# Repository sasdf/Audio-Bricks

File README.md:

Audio-Bricks
============

Building your own custom audio devices just like playing bricks

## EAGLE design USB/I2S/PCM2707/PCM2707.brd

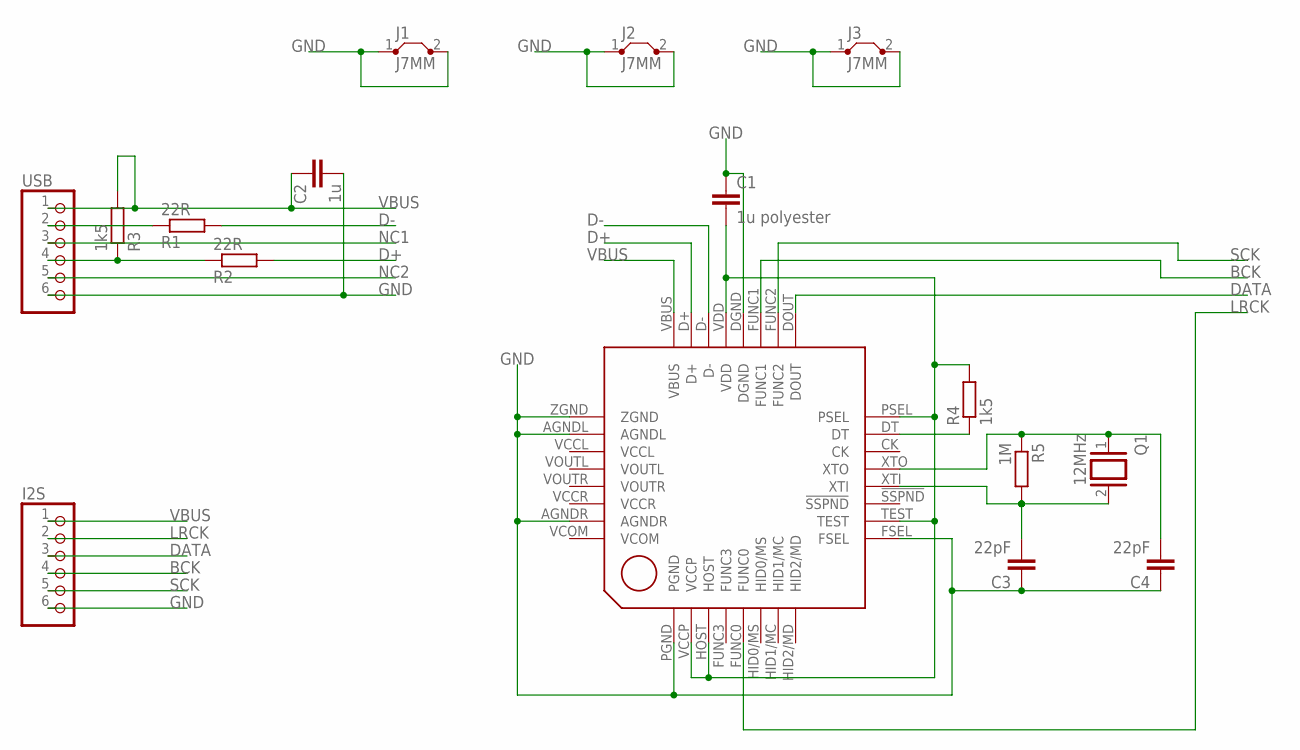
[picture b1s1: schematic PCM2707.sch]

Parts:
C1: 1u polyester; C5B4.5
C2: 1u; C5B3.5
C3, C4: 22pF; C5B3.5
I2S: PINHD-1X6/90; 1X06/90
J1, J2, J3: J7MM; 07
Q1: 12MHz; Q
R1, R2: 22R; 0207/7
R3, R4: 1k5; 0207/7
R5: 1M; 0207/7
U$1: PCM2706; TQFP32-08
USB: PINHD-1X6; 1X06

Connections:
BCK: I2S.4, U$1.FUNC1
D+: R2.2, U$1.D+
D-: R1.2, U$1.D-
DATA: I2S.3, U$1.DOUT
GND: C1.1, C2.2, C3.1, C4.1, I2S.6, J1.1, J1.2, J2.1, J2.2, J3.1, J3.2, U$1.AGNDL, U$1.AGNDR, U$1.DGND, U$1.FSEL, U$1.PGND, U$1.ZGND, USB.6
LRCK: I2S.2, U$1.FUNC0
unnamed: C1.2, R4.2, U$1.HOST, U$1.PSEL, U$1.TEST, U$1.VCCP, U$1.VDD
unnamed: R4.1, U$1.DT
unnamed: C4.2, Q1.1, R5.1, U$1.XTO
unnamed: R2.1, R3.1, USB.4
unnamed: C3.2, Q1.2, R5.2, U$1.XTI
unnamed: R1.1, USB.2
NC1: USB.3
NC2: USB.5
SCK: I2S.5, U$1.FUNC2
VBUS: C2.1, I2S.1, R3.2, U$1.VBUS, USB.1
VCCL: U$1.VCCL
VCCR: U$1.VCCR
VCOM: U$1.VCOM

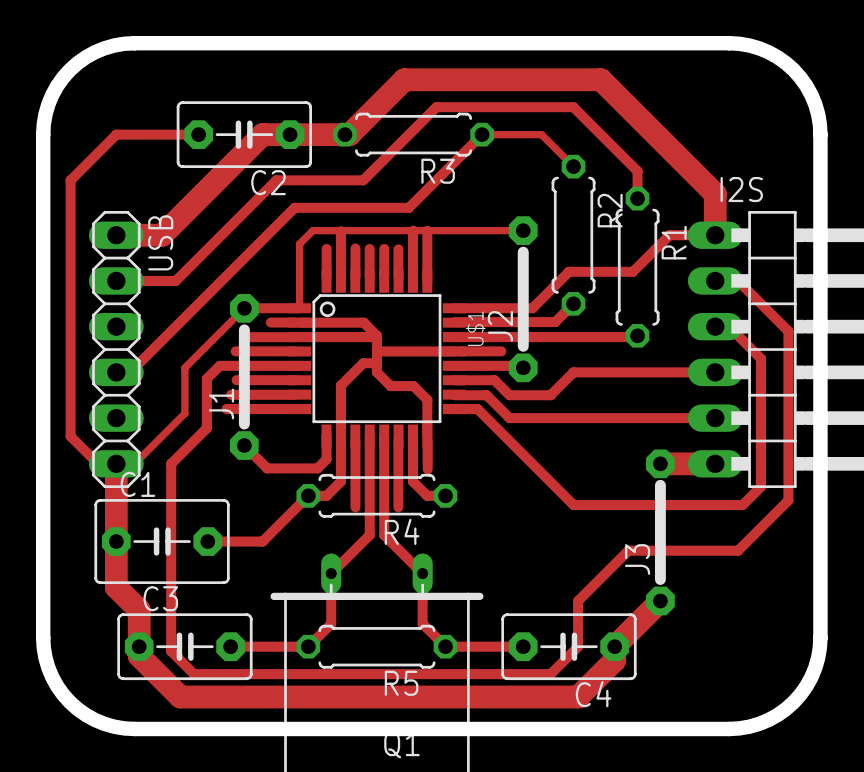
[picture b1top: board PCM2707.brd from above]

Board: 2 copper layers, 43.2 x 38.1 mm, 16 parts (0 on the bottom side), 14 nets.

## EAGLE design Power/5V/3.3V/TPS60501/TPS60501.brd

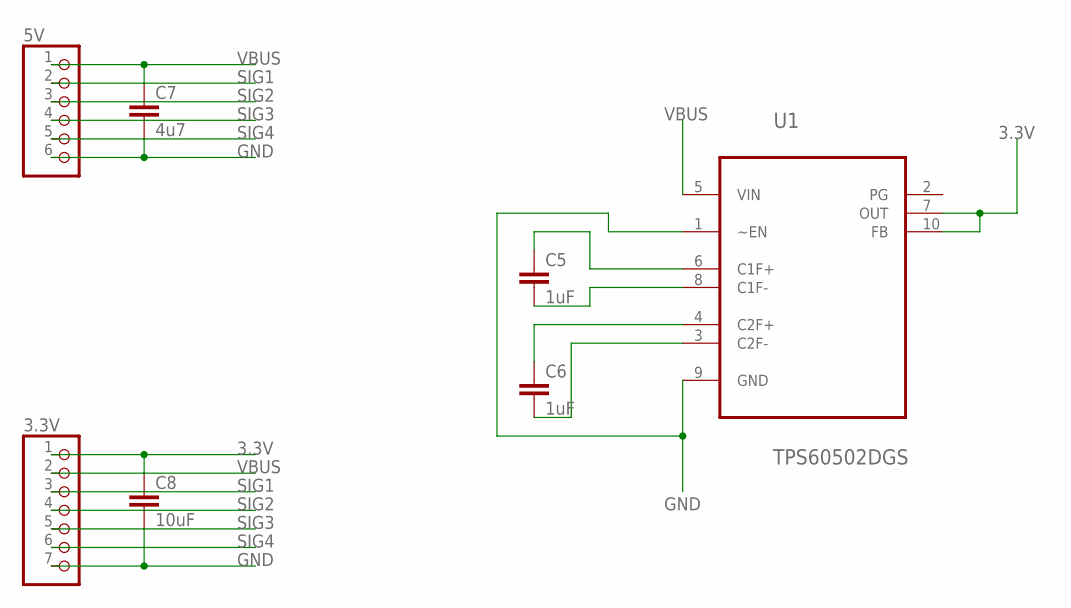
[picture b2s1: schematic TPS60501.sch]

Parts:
3.3V: PINHD-1X7; 1X07
5V: PINHD-1X6; 1X06
C5, C6: 1uF; C025-050X050
C7: 4u7; C025-050X050
C8: 10uF; C025-050X050
U1: TPS60502DGS; SOP50P490X110-10N

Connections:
3.3V: 3.3V.1, C8.1, U1.7 (OUT), U1.10 (FB)
GND: 3.3V.7, 5V.6, C7.2, C8.2, U1.1 (~EN), U1.9 (GND)
unnamed: C5.1, U1.6 (C1F+)
unnamed: C5.2, U1.8 (C1F-)
unnamed: C6.1, U1.4 (C2F+)
unnamed: C6.2, U1.3 (C2F-)
SIG1: 3.3V.3, 5V.2
SIG2: 3.3V.4, 5V.3
SIG3: 3.3V.5, 5V.4
SIG4: 3.3V.6, 5V.5
VBUS: 3.3V.2, 5V.1, C7.1, U1.5 (VIN)

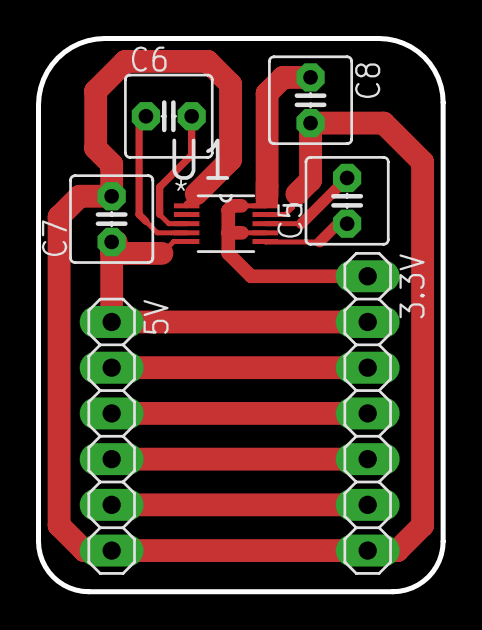
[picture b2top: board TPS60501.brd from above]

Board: 2 copper layers, 22.5 x 30.7 mm, 7 parts (0 on the bottom side), 11 nets.

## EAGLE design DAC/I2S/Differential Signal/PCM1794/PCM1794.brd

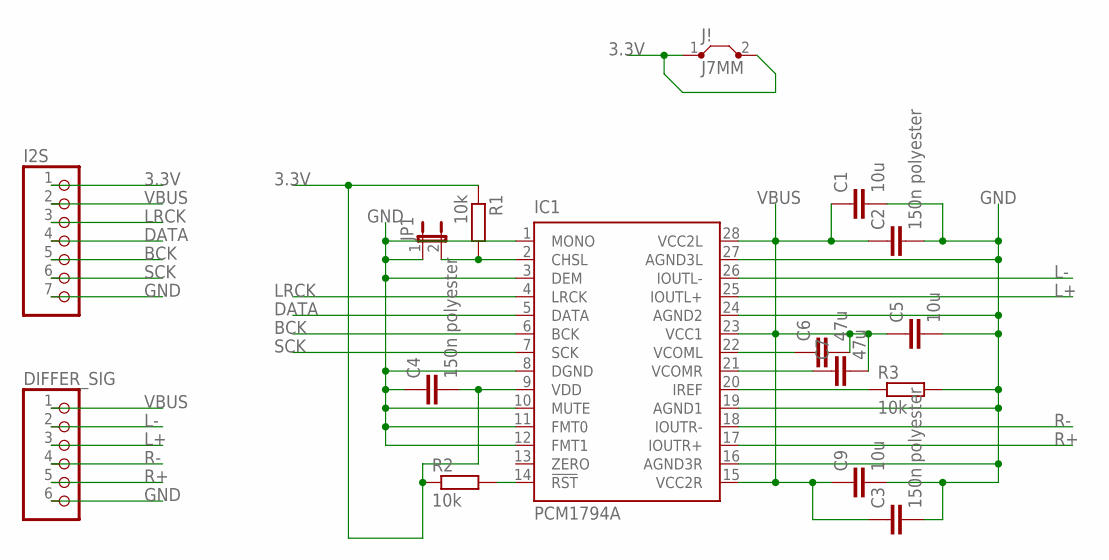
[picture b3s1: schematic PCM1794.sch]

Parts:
C1, C5, C9: 10u; C025-050X050
C2, C3, C4: 150n polyester; C7.5B4
C6, C7: 47u; C025-050X050
DIFFER_SIG: PINHD-1X6/90; 1X06/90
I2S: PINHD-1X7; 1X07
IC1: PCM1794A; DB_R-PDSO-G28
J!: J7MM; 07
JP1: JP1E; JP1
R1, R2, R3: 10k; 0207/7

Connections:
3.3V: C4.2, I2S.1, IC1.9 (VDD), J!.1, J!.2, R1.1, R2.1
BCK: I2S.5, IC1.6 (BCK)
DATA: I2S.4, IC1.5 (DATA)
GND: C1.2, C2.2, C3.2, C4.1, C5.2, C9.2, DIFFER_SIG.6, I2S.7, IC1.1 (MONO), IC1.3 (DEM), IC1.8 (DGND), IC1.10 (MUTE), IC1.11 (FMT0), IC1.12 (FMT1), IC1.16 (AGND3R), IC1.19 (AGND1), IC1.24 (AGND2), IC1.27 (AGND3L), JP1.1, R3.2
L+: DIFFER_SIG.3, IC1.25 (IOUTL+)
L-: DIFFER_SIG.2, IC1.26 (IOUTL-)
LRCK: I2S.3, IC1.4 (LRCK)
unnamed: C6.1, IC1.22 (VCOML)
unnamed: C7.1, IC1.21 (VCOMR)
unnamed: IC1.2 (CHSL), JP1.2, R1.2
unnamed: IC1.20 (IREF), R3.1
unnamed: IC1.14 (!RST), R2.2
R+: DIFFER_SIG.5, IC1.17 (IOUTR+)
R-: DIFFER_SIG.4, IC1.18 (IOUTR-)
SCK: I2S.6, IC1.7 (SCK)
VBUS: C1.1, C2.1, C3.1, C5.1, C6.2, C7.2, C9.1, DIFFER_SIG.1, I2S.2, IC1.15 (VCC2R), IC1.23 (VCC1), IC1.28 (VCC2L)

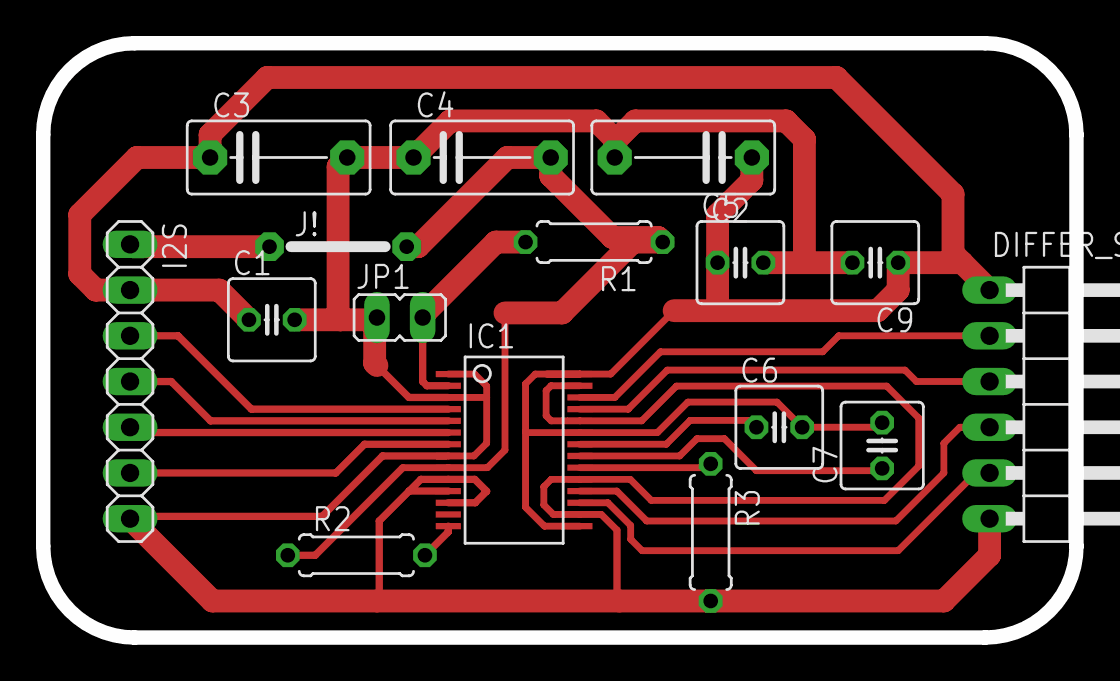
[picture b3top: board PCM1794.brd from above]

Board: 2 copper layers, 57.4 x 33.0 mm, 16 parts (0 on the bottom side), 16 nets.

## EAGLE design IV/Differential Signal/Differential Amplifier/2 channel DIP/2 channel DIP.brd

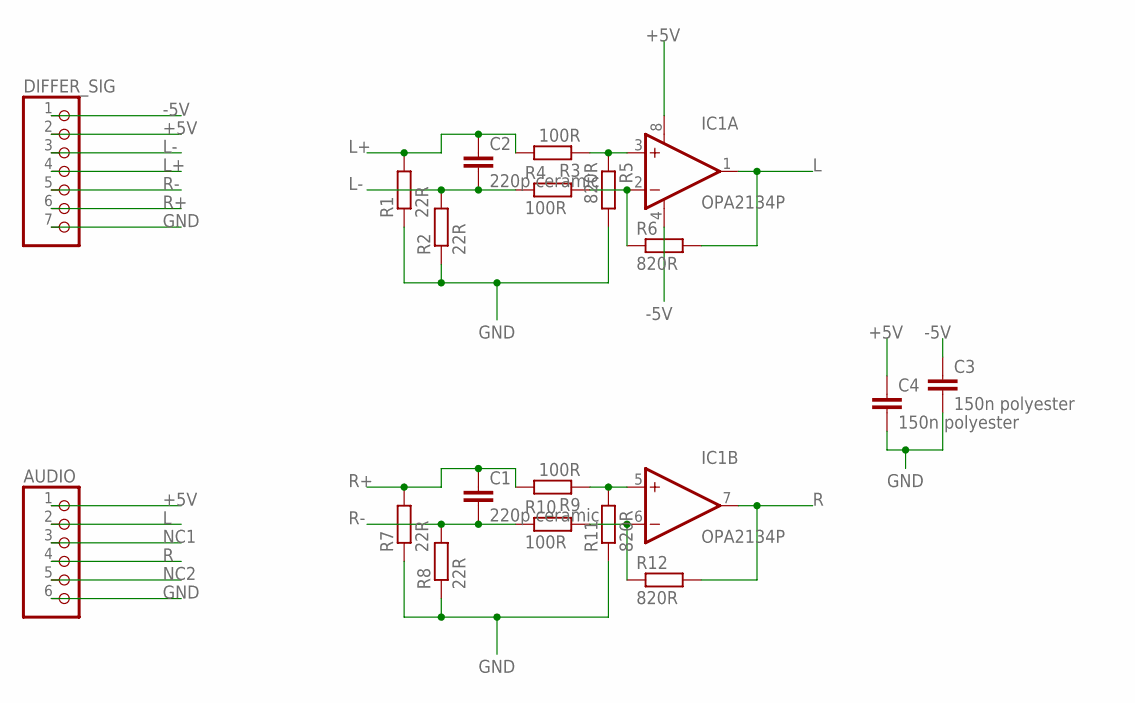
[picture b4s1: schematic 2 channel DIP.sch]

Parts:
AUDIO: PINHD-1X6; 1X06
C1, C2: 220p ceramic; C050-030X075
C3, C4: 150n polyester; C050-030X075
DIFFER_SIG: PINHD-1X7; 1X07
IC1: OPA2134P; DIL08
R1, R2, R7, R8: 22R; 0207/7
R3, R4, R9, R10: 100R; 0207/7
R5, R6, R11, R12: 820R; 0207/7

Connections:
+5V: AUDIO.1, C4.1, DIFFER_SIG.2, IC1.8 (V+)
-5V: C3.1, DIFFER_SIG.1, IC1.4 (V-)
GND: AUDIO.6, C3.2, C4.2, DIFFER_SIG.7, R1.1, R2.1, R5.2, R7.1, R8.1, R11.1
L: AUDIO.2, IC1.1 (OUT), R6.2
L+: C2.1, DIFFER_SIG.4, R1.2, R3.2
L-: C2.2, DIFFER_SIG.3, R2.2, R4.1
unnamed: IC1.3 (+IN), R3.1, R5.1
unnamed: IC1.2 (-IN), R4.2, R6.1
unnamed: IC1.5 (+IN), R9.1, R11.2
unnamed: IC1.6 (-IN), R10.2, R12.1
NC1: AUDIO.3
NC2: AUDIO.5
R: AUDIO.4, IC1.7 (OUT), R12.2
R+: C1.1, DIFFER_SIG.6, R7.2, R9.2
R-: C1.2, DIFFER_SIG.5, R8.2, R10.1

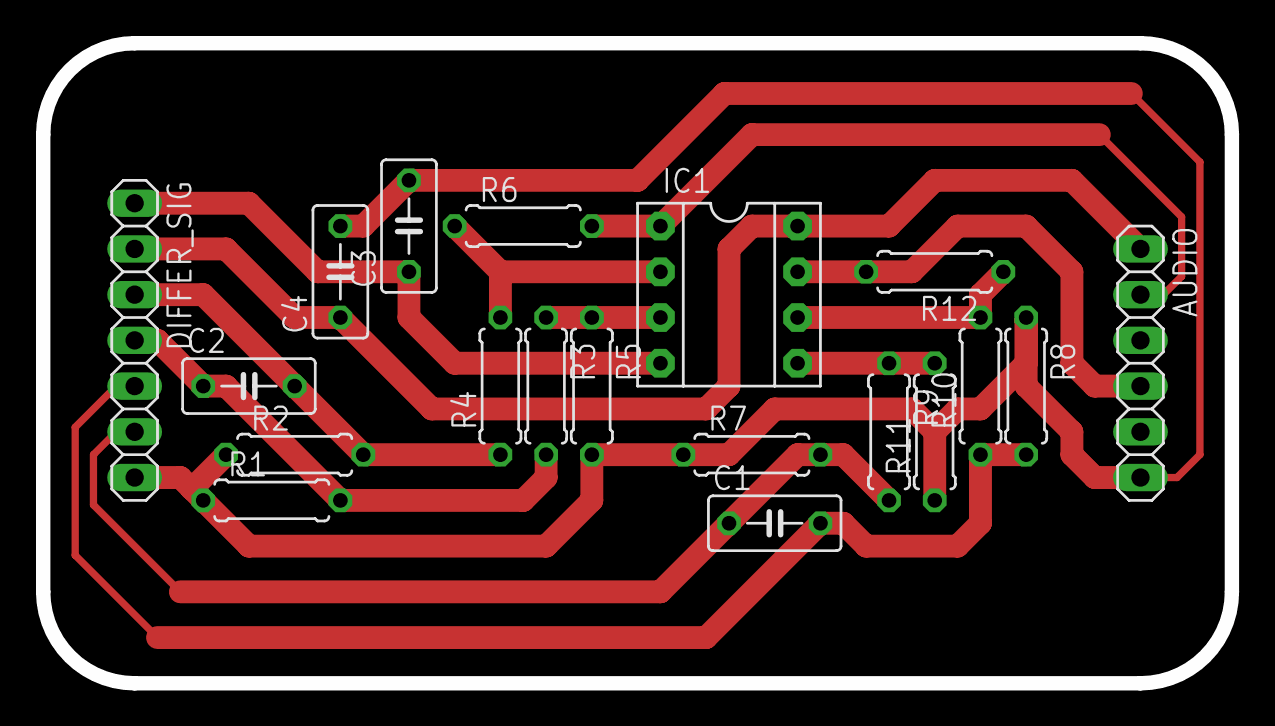
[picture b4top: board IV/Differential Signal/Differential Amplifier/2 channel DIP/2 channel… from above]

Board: 2 copper layers, 66.0 x 35.6 mm, 19 parts (0 on the bottom side), 13 nets.

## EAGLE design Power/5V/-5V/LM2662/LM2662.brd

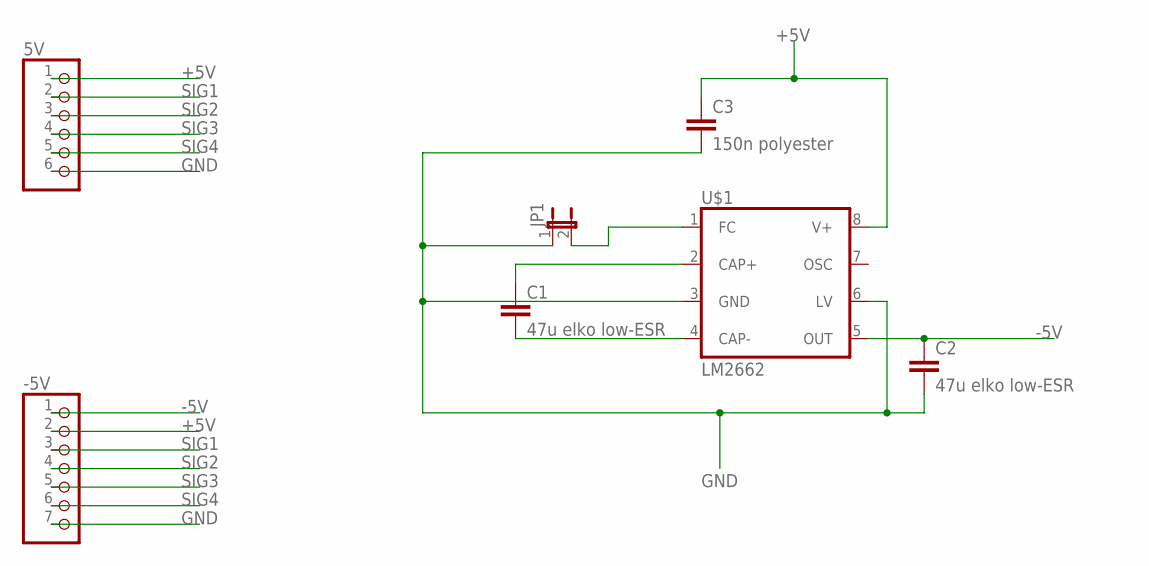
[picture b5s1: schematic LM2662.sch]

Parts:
5V: PINHD-1X6; 1X06
-5V: PINHD-1X7; 1X07
C1, C2: 47u elko low-ESR; C025-050X050
C3: 150n polyester; C050-030X075
JP1: JP1E; JP1
U$1: LM2662; SOIC8

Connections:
+5V: 5V.1, -5V.2, C3.1, U$1.8 (V+)
-5V: -5V.1, C2.1, U$1.5 (OUT)
GND: 5V.6, -5V.7, C2.2, C3.2, JP1.1, U$1.3 (GND), U$1.6 (LV)
unnamed: JP1.2, U$1.1 (FC)
unnamed: C1.1, U$1.2 (CAP+)
unnamed: C1.2, U$1.4 (CAP-)
SIG1: 5V.2, -5V.3
SIG2: 5V.3, -5V.4
SIG3: 5V.4, -5V.5
SIG4: 5V.5, -5V.6

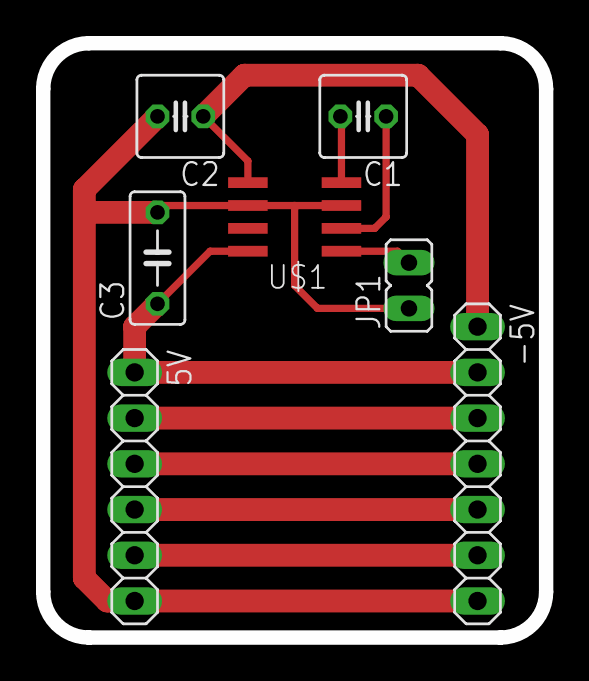
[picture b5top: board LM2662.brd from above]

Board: 2 copper layers, 27.9 x 33.0 mm, 7 parts (0 on the bottom side), 10 nets.

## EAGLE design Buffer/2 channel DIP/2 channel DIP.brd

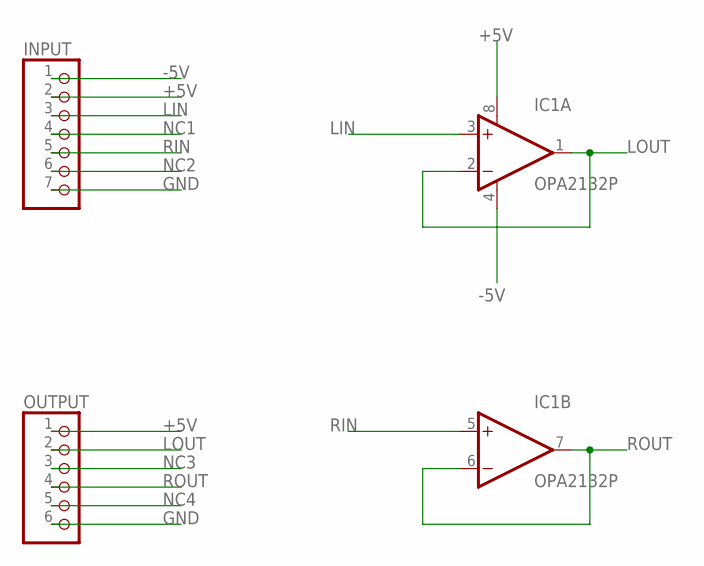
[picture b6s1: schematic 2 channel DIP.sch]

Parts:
IC1: OPA2132P; DIL08
INPUT: PINHD-1X7; 1X07
OUTPUT: PINHD-1X6; 1X06

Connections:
+5V: IC1.8 (V+), INPUT.2, OUTPUT.1
-5V: IC1.4 (V-), INPUT.1
GND: INPUT.7, OUTPUT.6
LIN: IC1.3 (+IN), INPUT.3
LOUT: IC1.1 (OUT), IC1.2 (-IN), OUTPUT.2
NC1: INPUT.4
NC2: INPUT.6
NC3: OUTPUT.3
NC4: OUTPUT.5
RIN: IC1.5 (+IN), INPUT.5
ROUT: IC1.6 (-IN), IC1.7 (OUT), OUTPUT.4

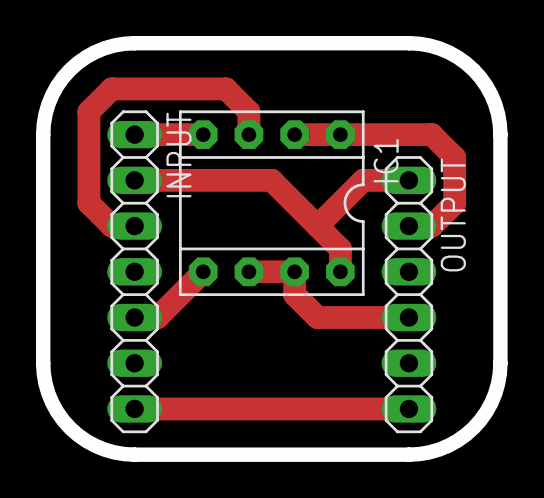
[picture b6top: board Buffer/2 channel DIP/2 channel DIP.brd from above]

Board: 2 copper layers, 25.4 x 22.9 mm, 3 parts (0 on the bottom side), 7 nets.

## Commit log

2014-06-15 Initial commit
    Added USB -> I2S (PCM2707).
    Added I2S -> Differential Signal (PCM1794A).
    Added Differential Signal -> Audio (OPAMP(DIP 2ch)).
    Added Buffer (OPAMP(DIP 2ch)).
    Added +5v -> +3.3v (TPS60501).
    Added +5v -> -5v (LM2662).
2014-06-19 Made PCM2707's pad longer
2014-06-19 Wire width change
